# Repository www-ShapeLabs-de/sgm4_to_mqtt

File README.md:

# ESP8266 electricity meter reading head for SGM-C4 meter with homeassistant mqtt-discovery

## Introduction
This project represents a complete electricity meter reading head for the SGM-C4 meter based on ESP8266. No other hardware like a Raspberry-Pi or similar is needed except for the hardware mentioned here. This read head is specially developed for homeassistant, but can also be used for other home automation systems via manual MQTT configuration.
The SML data set is read from the SGM-C4 meter via the optical interface and decoded. The data is transferred to homeassistant via MQTT. At startup, the read head automatically sets itself up as a device via mqtt-discovery with all its entities.

## Hardware

### Electronics
All components are easy to obtain, the optical TX side (U5, Q2, D1, R7, C10) can also remain unpopulated. Currently it is not used. When choosing the IR receiving diode (Q3) the SFH309 should be used. With other diodes there could be problems. Otherwise the circuit is quite trivial and should be easy to build and populate. Board data are available as KiCad files in the repo. For standard-use it's necessary to set Jumper JP2 to 1-2

### Housing
CAD data for a housing is available as a STEP file. There are also STL files that can be printed directly. If no printer is available, the circuit board can also be attached to the electricity meter with double-sided adhesive tape and a few plastic plates (approx. 3 mm thick) as a spacer block.

## Software / Config
For this project it is necessary to enable the complete data output of the electricity meter by means of a PIN code. You can get the PIN code from your metering point operator (in german: "Messstellenbetreiber"), a phone call is sufficient. The metering point operator is obliged to provide the PIN code. For this purpose, you should have the customer data and the meter number available.

### Entering the PIN code
To enter the PIN, you must first press the mechanical key once. After that, the PIN display appears in the lower display line and the first digit appears with a
"0". To enter your PIN, press the key repeatedly until the value of the first digit of your personal PIN appears in the display. After a short waiting time the device is ready (display of a "0") for the input of the 2nd digit of your PIN. Enter the corresponding value of your personal PIN here as well. Then repeat the entry procedure for the 3rd and 4th digits of your PIN in the same way. 

### Configuration of the software
The WLAN access data must be entered in the #define area of the software. In addition, the address or IP of the MQTT broker and its access data are required.
Under "Location" and "Name" the device name as well as its installation location can be assigned. This also results in the MQTT topic. 

```
#define SOFTWARE_VERSION      "v1.4"
#define WLAN_SSID             "myssid"
#define WLAN_PASS             "mywifipasswd"
#define MQTT_SERVER           "192.168.1.2"
#define MQTT_SERVERPORT       1883 					// use 8883 for SSL
#define MQTT_USERNAME         "mqttuser"
#define MQTT_KEY              "mosquitto"
#define LOCATION              "my_location"
#define NAME                  "E_Meter"
//#define OTA_PASS            "admin"
#define STATE_UPDATE_INTERVAL 5000 					// MQTT state update interval in [ms] (<5000ms could be critical for parsing in worst case)
#define AVAILABILITY_ONLINE   "online"
#define AVAILABILITY_OFFLINE  "offline"
```

Afterwards the software can be flashed to the ESP8266 with a mini-USB cable and the Arduino IDE. To enter the flash mode, the flash button must be held down while pressing the reset button. After the flash process, the ESP should be reset again.

After that the device should be found automatically in HASSIO with all its entities:

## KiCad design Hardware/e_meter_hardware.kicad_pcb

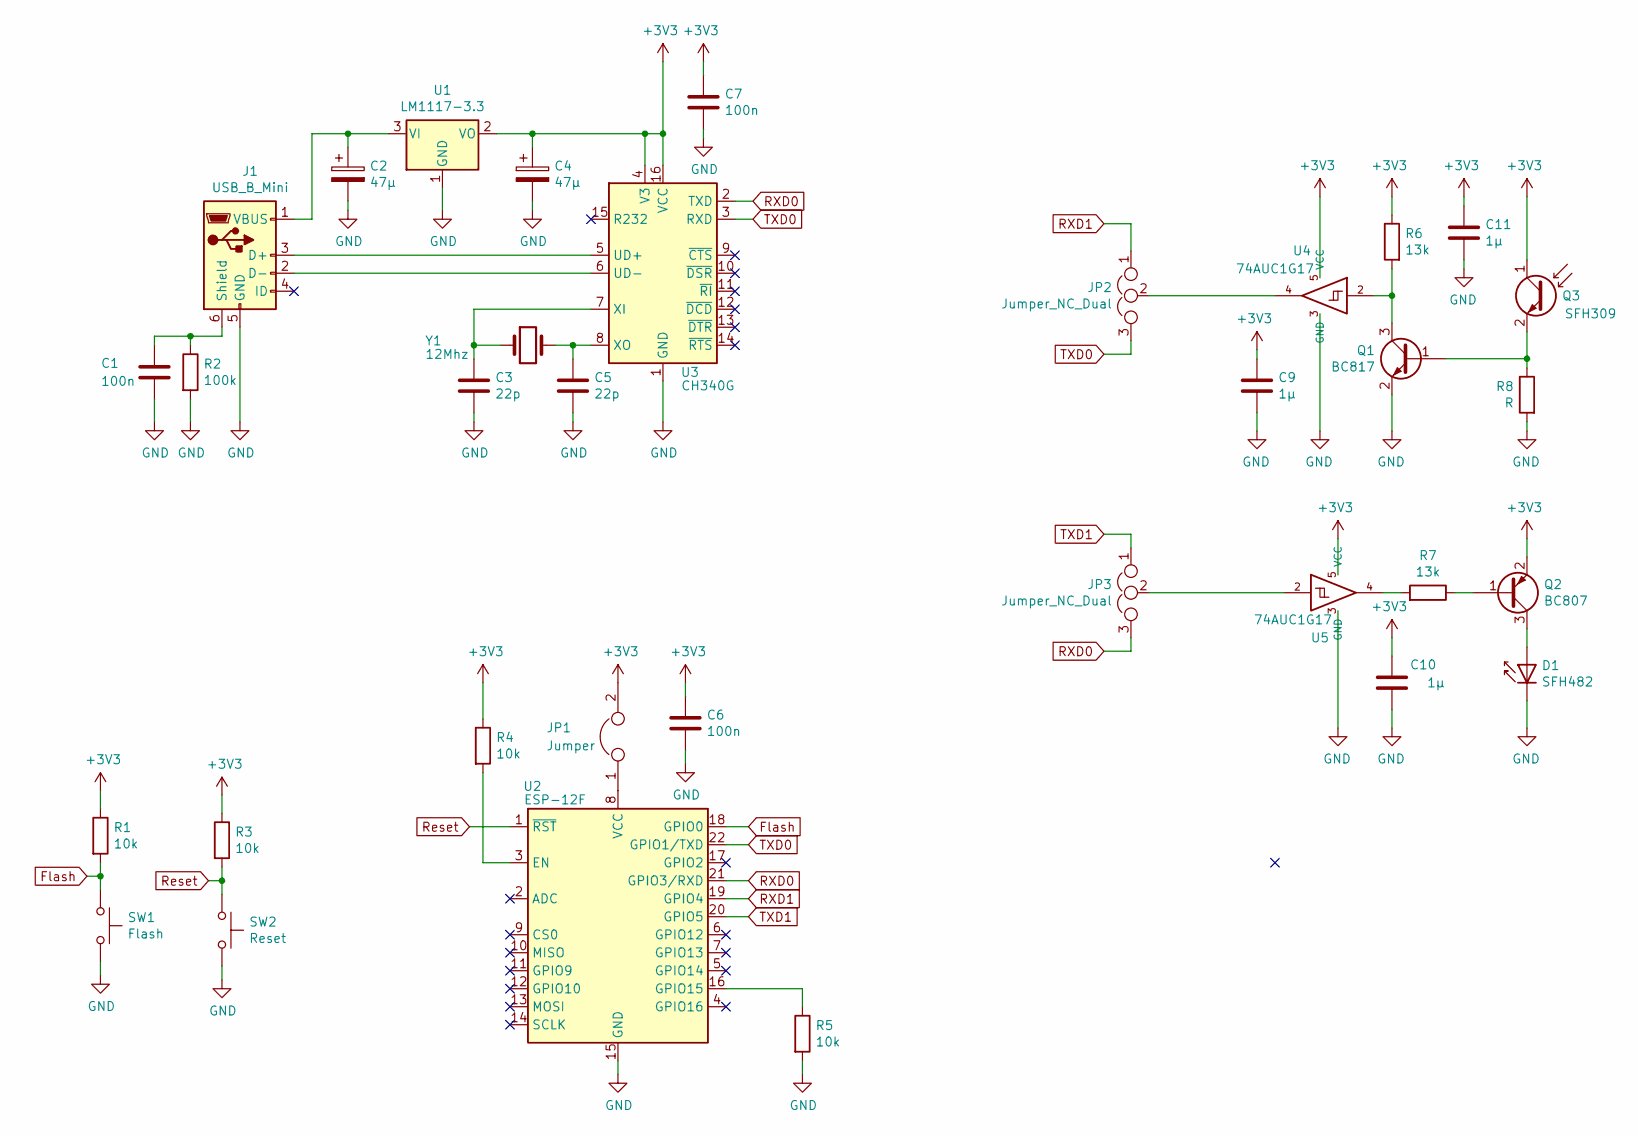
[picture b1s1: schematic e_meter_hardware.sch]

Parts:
C1, C6, C7: 100n; C_0805_2012Metric
C2, C4: 47µ; CP_EIA-3528-21_Kemet-B
C3, C5: 22p; C_0805_2012Metric
C9, C10, C11: 1µ; C_0805_2012Metric
D1: SFH482; LED_D3.0mm_Clear
J1: USB_B_Mini; USB_Mini-B_Wuerth_65100516121_Horizontal
JP1: Jumper; SolderJumper-2_P1.3mm_Open_RoundedPad1.0x1.5mm
JP2, JP3: Jumper_NC_Dual; SolderJumper-3_P1.3mm_Open_RoundedPad1.0x1.5mm
Q1: BC817; SOT-23
Q2: BC807; SOT-23
Q3: SFH309; LED_D3.0mm_Clear
R1, R3, R4, R5: 10k; R_0805_2012Metric
R2: 100k; R_0805_2012Metric
R6, R7: 13k; R_0805_2012Metric
R8: R; R_0805_2012Metric
SW1: Flash; SW_Push_1P1T_NO_6x6mm_H9.5mm
SW2: Reset; SW_Push_1P1T_NO_6x6mm_H9.5mm
U1: LM1117-3.3; SOT-223-3_TabPin2
U2: ESP-12F; ESP-12E
U3: CH340G; SOIC-16_3.9x9.9mm_P1.27mm
U4, U5: 74AUC1G17; SOT-23-5
Y1: 12Mhz; Crystal_HC49-U_Vertical

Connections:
+3V3: C4.1, C6.1, C7.1, C9.1, C10.1, C11.1, JP1.2, Q2.2 (E), Q3.1 (C), R1.1, R3.1, R4.1, R6.1, U1.2 (VO), U3.4 (V3), U3.16 (VCC), U4.5 (VCC), U5.5 (VCC)
Flash: R1.2, SW1.1, U2.18 (GPIO0)
GND: C1.2, C2.2, C3.2, C4.2, C5.2, C6.2, C7.2, C9.2, C10.2, C11.2, D1.1 (K), J1.5 (GND), Q1.2 (E), R2.2, R5.2, R8.2, SW1.2, SW2.2, U1.1 (GND), U2.15 (GND), U3.1 (GND), U4.3 (GND), U5.3 (GND)
unnamed: C1.1, J1.6 (Shield), R2.1
unnamed: C2.1, J1.1 (VBUS), U1.3 (VI)
unnamed: C3.1, U3.7 (XI), Y1.1
unnamed: C5.1, U3.8 (XO), Y1.2
unnamed: D1.2 (A), Q2.3 (C)
unnamed: J1.2 (D-), U3.6 (UD-)
unnamed: J1.3 (D+), U3.5 (UD+)
unnamed: JP1.1, U2.8 (VCC)
unnamed: JP2.2, U4.4
unnamed: JP3.2, U5.2
unnamed: Q1.1 (B), Q3.2 (E), R8.1
unnamed: Q1.3 (C), R6.2, U4.2
unnamed: Q2.1 (B), R7.1
unnamed: R4.2, U2.3 (EN)
unnamed: R5.1, U2.16 (GPIO15)
unnamed: R7.2, U5.4
RXD0: JP3.3, U2.21 (GPIO3/RXD), U3.2 (TXD)
RXD1: JP2.1, U2.19 (GPIO4)
Reset: R3.2, SW2.1, U2.1 (~RST)
TXD0: JP2.3, U2.22 (GPIO1/TXD), U3.3 (RXD)
TXD1: JP3.1, U2.20 (GPIO5)

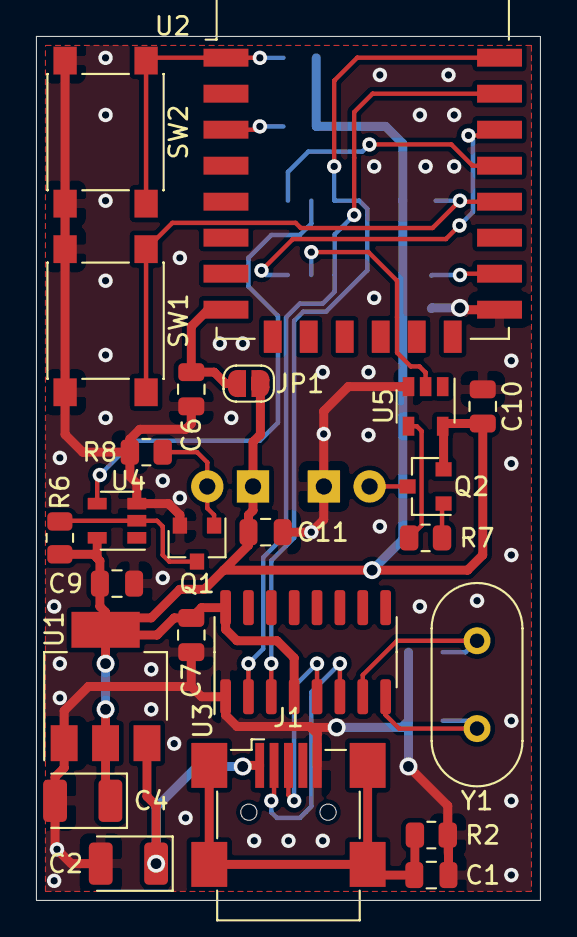
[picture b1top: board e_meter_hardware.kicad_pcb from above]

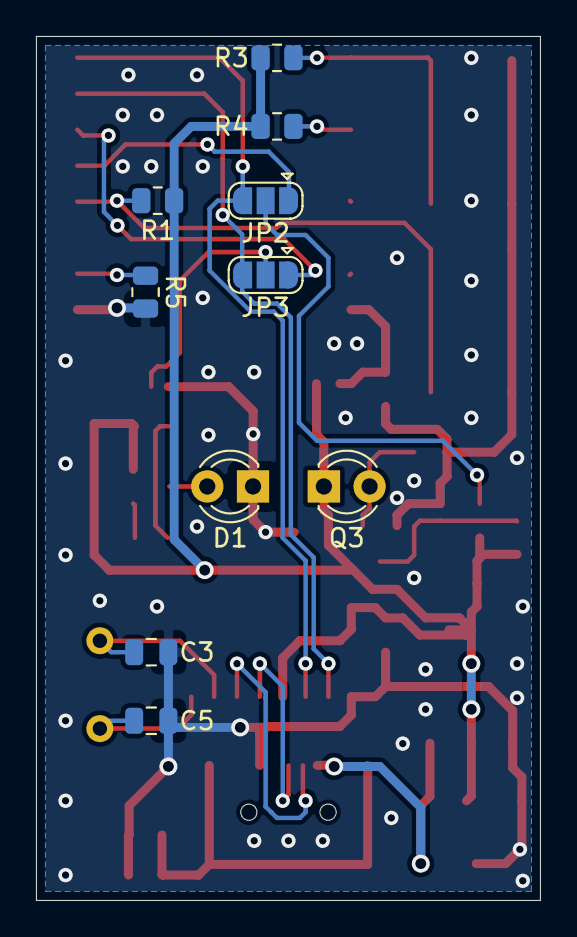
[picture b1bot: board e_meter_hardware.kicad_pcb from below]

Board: 2 copper layers, 28.0 x 48.0 mm, 34 parts (10 on the bottom side), 24 nets.

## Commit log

2023-02-16 pics added
2023-02-16 Update README.md
    some text formatting
2024-07-31 photo modified
2024-08-02 New Version of Software, SML parser improved
